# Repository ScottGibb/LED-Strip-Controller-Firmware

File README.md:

# LED Strip Controller Firmware

<!-- markdown-link-check-disable -->
   
<!-- markdown-link-check-enable -->

## Summary

This repository contains all the firmware to control the LED Strip Controller Hardware variations. The firmware is written in C++ using the Arduino framework, originally I wanted to use the STM32 HAL Drivers, however, the STM32 Microcontrollers were cloned and this resulted in the Arduino framework being used. The firmware is designed to be as flexible as possible, whilst maintaining an easy-to-use interface. The firmware is designed to be used with the LED Strip Controller Software Applications that are described below. The firmware is designed to be used with different microcontrollers.

## System Architecture

As for the system architecture it's designed to be interacted with via a byte stream sent over an interface. At present there is a UART interface over USB. However, there are plans to utilize an IP interface over WiFi. The byte stream is then parsed by the firmware and the appropriate action is taken. The firmware is designed to be as flexible as possible, whilst maintaining an easy-to-use interface. The firmware is designed to be used with the LED Strip Controller Software Applications. The architecture of the full system is shown below:

## Project Structure

This Project uses the PlatformIO Build system and as such adheres to their build structure and folder structure, the project is split into multiple folders outlined as follows:

```shell
├───docs
├───include
├───lib
│   ├───Board Configurations
│   ├───Buttons
│   ├───Communications
│   ├───Communicators
│   ├───Light Drivers
│   ├───Light Handlers
│   ├───Memory Management
│   ├───Misc Peripherals
│   ├───System Configuration
│   ├───System State Management
│   └───User Mode Handlers
├───src
└───test
```

- docs: holds all diagrams and pictures related to the project
- include: Holds the main header file responsible for the high-level aspects of the project
- lib: contains all private libraries for the project.
- src: contains the main application source code
- test: contains all of the unit tests for the project.

## Firmware Design

The firmware is designed to utilize modern C++ principles and be fully object orientated. This was done to allow me to utilize the full power of the C++ language and also allow me to learn new features regarding the language. The class diagram for the firmware is shown below:

The firmware is split into multiple layers which follow this layer convention:

The idea behind this is that the Arduino layer is abstracted away from the rest of the firmware. This allows the firmware logic to be used across multiple platforms and prevents it from being tied into the Arduino framework.

## Memory Map

The system does require some onboard memory to utilize the User Mode system. This allows the user to create custom colour waveforms and thus create custom effects. The memory map for the STM32F103C8T6 microcontroller is shown below:

## Building the Project

This project uses the PlatformIO Build system and as such can be built using the PlatformIO IDE or the PlatformIO CLI. For this simply clone this repository and open the folder using the PlatformIO plugin in VSCode. The IDE should then flag and install all the dependencies based on the platform.ini file.

- [PlatformIO](https://platformio.org/)
- [Visual Studio Code](https://code.visualstudio.com/)
- [PlatformIO Plugin for VSCode](https://marketplace.visualstudio.com/items?itemName=platformio.platformio-ide)

## Linting the project

You will need NodeJS and Docker installed. Once these are installed you can run the following command to lint the project:

```bash
npx mega-linter-runner
```

## LED Strip Controller Repository Links

- [Manifest](https://github.com/ScottGibb/LED-Strip-Controller-Manifest) This repository contains the manifest file for the LED Strip Controller project. Which allows the cloning of all the repositories in one go.
- [Hardware](https://github.com/ScottGibb/LED-Strip-Controller-Hardware) This repository contains the hardware design files for the LED Strip Controller project.
- [Firmware](https://github.com/ScottGibb/LED-Strip-Controller-Firmware) This repository contains the firmware for the LED Strip Controller project.
- [Software](https://github.com/ScottGibb/LED-Strip-Controller-Software) This repository contains the software for the LED Strip Controller project.

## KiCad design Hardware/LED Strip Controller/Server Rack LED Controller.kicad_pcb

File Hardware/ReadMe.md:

# LED Strip Controller Hardware
# Summary
The hardware was developed using veroboard first to prove the concept and then a PCB was designed with extra features that include: reduced form factor, over current/voltage protection circuitry, better thermal and EMI management.
# Design
The design consists of two PCBs, one which is the LED controller and an optional Buttons Controller daughter board. The 3D Printed case utilises both however, if the user decided that they only wanted to use the device through USB then the board could be removed.

## LED Strip Controller

The LED Strip Controller hardware is responsible for controlling the LEDs along with maintaining the system. This hardware should be capable of driving a variety of different light strips and protecting the whole board from short circuits and over voltages. The 3D render of the PCB is shown below:

## Buttons Controller
As for the Buttons Controller board, this is a simple PCB board with buttons, that can be added to the main board through a simple ribbon cable. This is done so that optional buttons can be added to the system. The 3D render of the PCB is shown below:

## 3D Printed Case Assembly

As for containing the hardware, a 3D printable case was designed and is shown below:

## Cable Wiring

# Improvements

# Useful Links
- [XT60 Connectors](https://www.aliexpress.com/item/1005004111518826.html?spm=a2g0o.order_list.0.0.44851802WtcK2c)
- [Terminal Crimps](https://www.aliexpress.com/item/1005004040825209.html?spm=a2g0o.productlist.0.0.7b09618cNrzGIX&algo_pvid=1400a7b4-9197-4d6a-b152-92a1a64300d6&algo_exp_id=1400a7b4-9197-4d6a-b152-92a1a64300d6-1&pdp_ext_f=%7B%22sku_id%22%3A%2212000028334234012%22%7D&pdp_npi=2%40dis%21GBP%216.94%215.2%21%21%21%21%21%402100bddb16647521768224542ea791%2112000028334234012%21sea&curPageLogUid=0NObb2zgCZaC)
- [Ferrel Crimps](https://www.aliexpress.com/item/1005004283026574.html?spm=a2g0o.detail.1000060.1.2b025a79uxZBof&gps-id=pcDetailBottomMoreThisSeller&scm=1007.13339.291025.0&scm_id=1007.13339.291025.0&scm-url=1007.13339.291025.0&pvid=82c1f2f2-f4eb-4113-b474-5a5eedb67d54&_t=gps-id:pcDetailBottomMoreThisSeller,scm-url:1007.13339.291025.0,pvid:82c1f2f2-f4eb-4113-b474-5a5eedb67d54,tpp_buckets:668%232846%238114%231999&pdp_ext_f=%7B%22sku_id%22%3A%2212000028621229126%22%2C%22sceneId%22%3A%223339%22%7D&pdp_npi=2%40dis%21GBP%218.57%215.57%21%21%21%21%21%40211b444016647521812691593e8c0a%2112000028621229126%21rec)
- [Switches](https://www.aliexpress.com/item/32743866390.html?spm=a2g0o.productlist.0.0.3cd4700cNdYXJ6&algo_pvid=e6b88297-a8ce-45f8-93eb-8b976bdea822&algo_exp_id=e6b88297-a8ce-45f8-93eb-8b976bdea822-3&pdp_ext_f=%7B%22sku_id%22%3A%2212000029574447281%22%7D&pdp_npi=2%40dis%21GBP%210.39%210.25%21%21%210.82%21%21%400b0a0ae216647521586066114e5989%2112000029574447281%21sea&curPageLogUid=3X8Abgou2M2X)

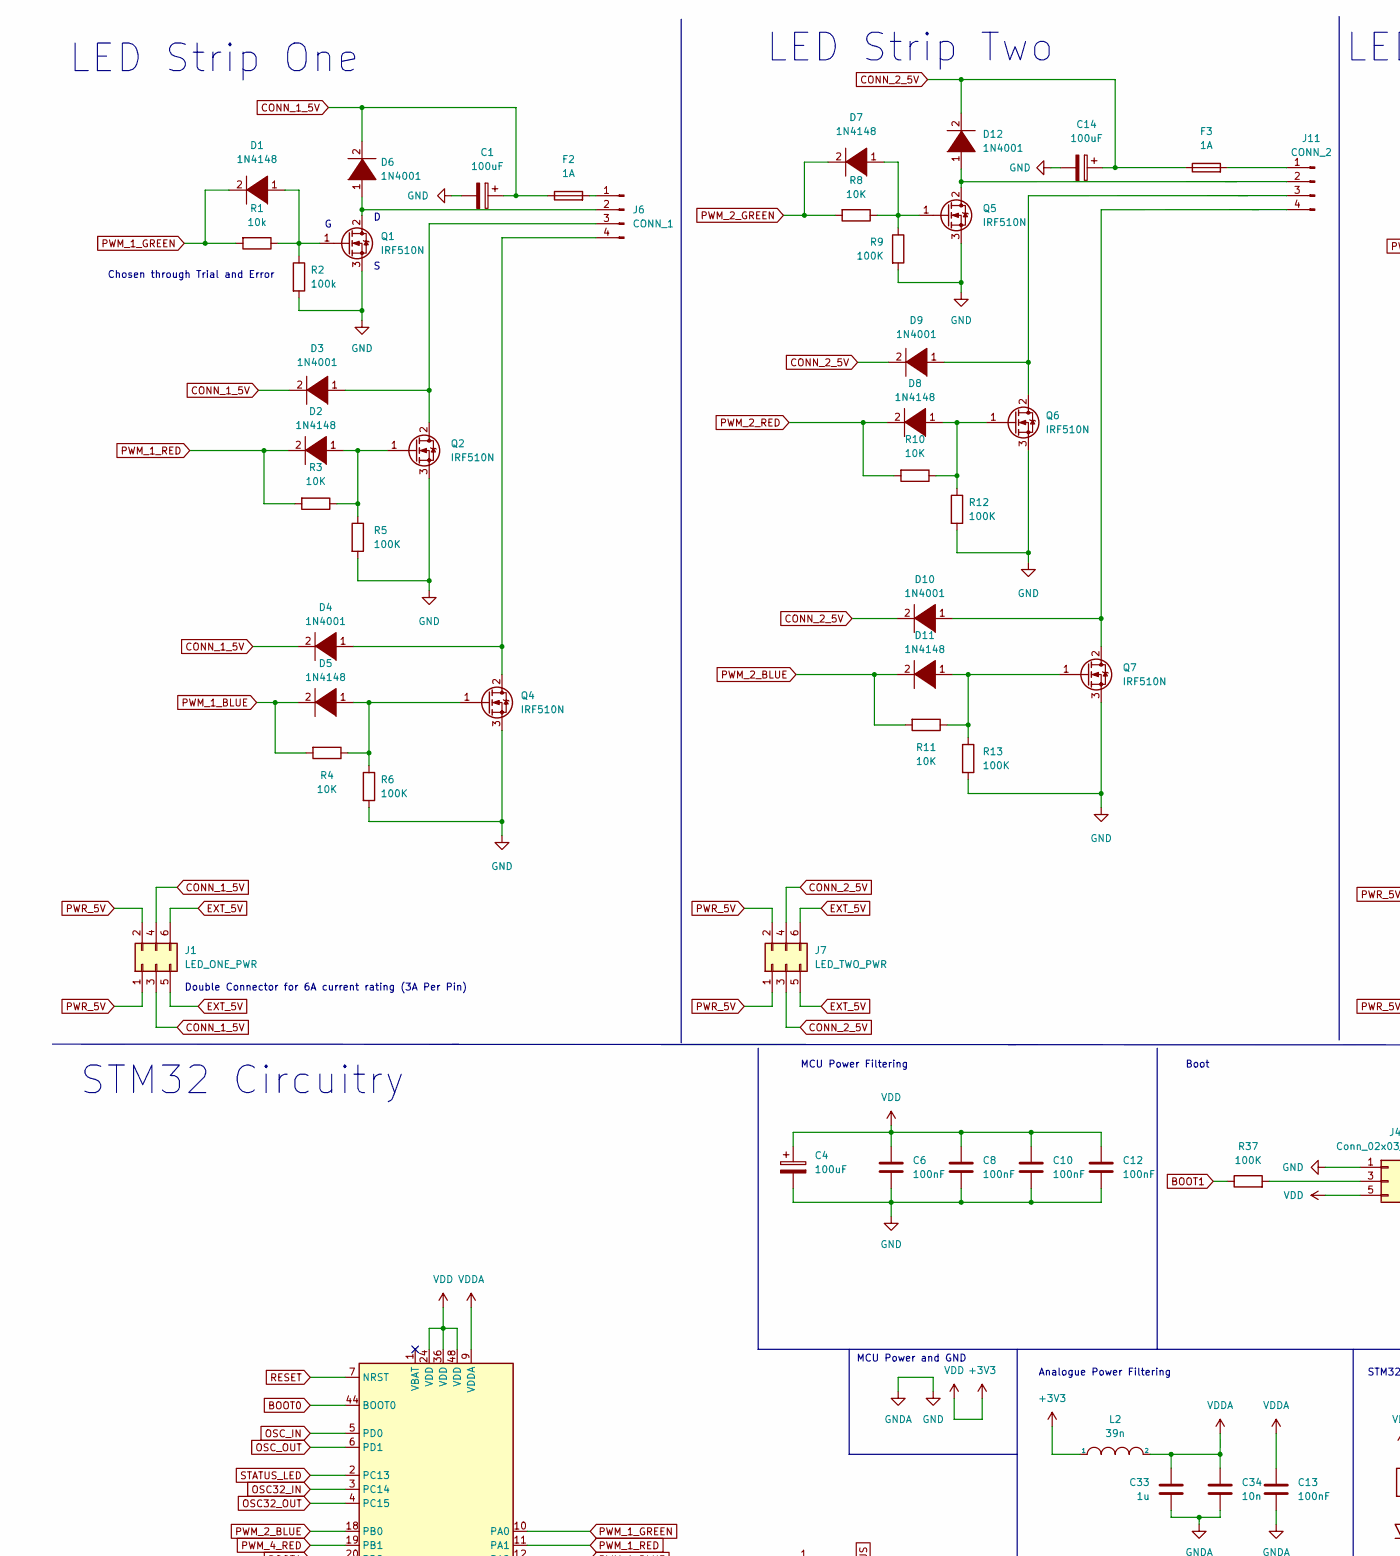
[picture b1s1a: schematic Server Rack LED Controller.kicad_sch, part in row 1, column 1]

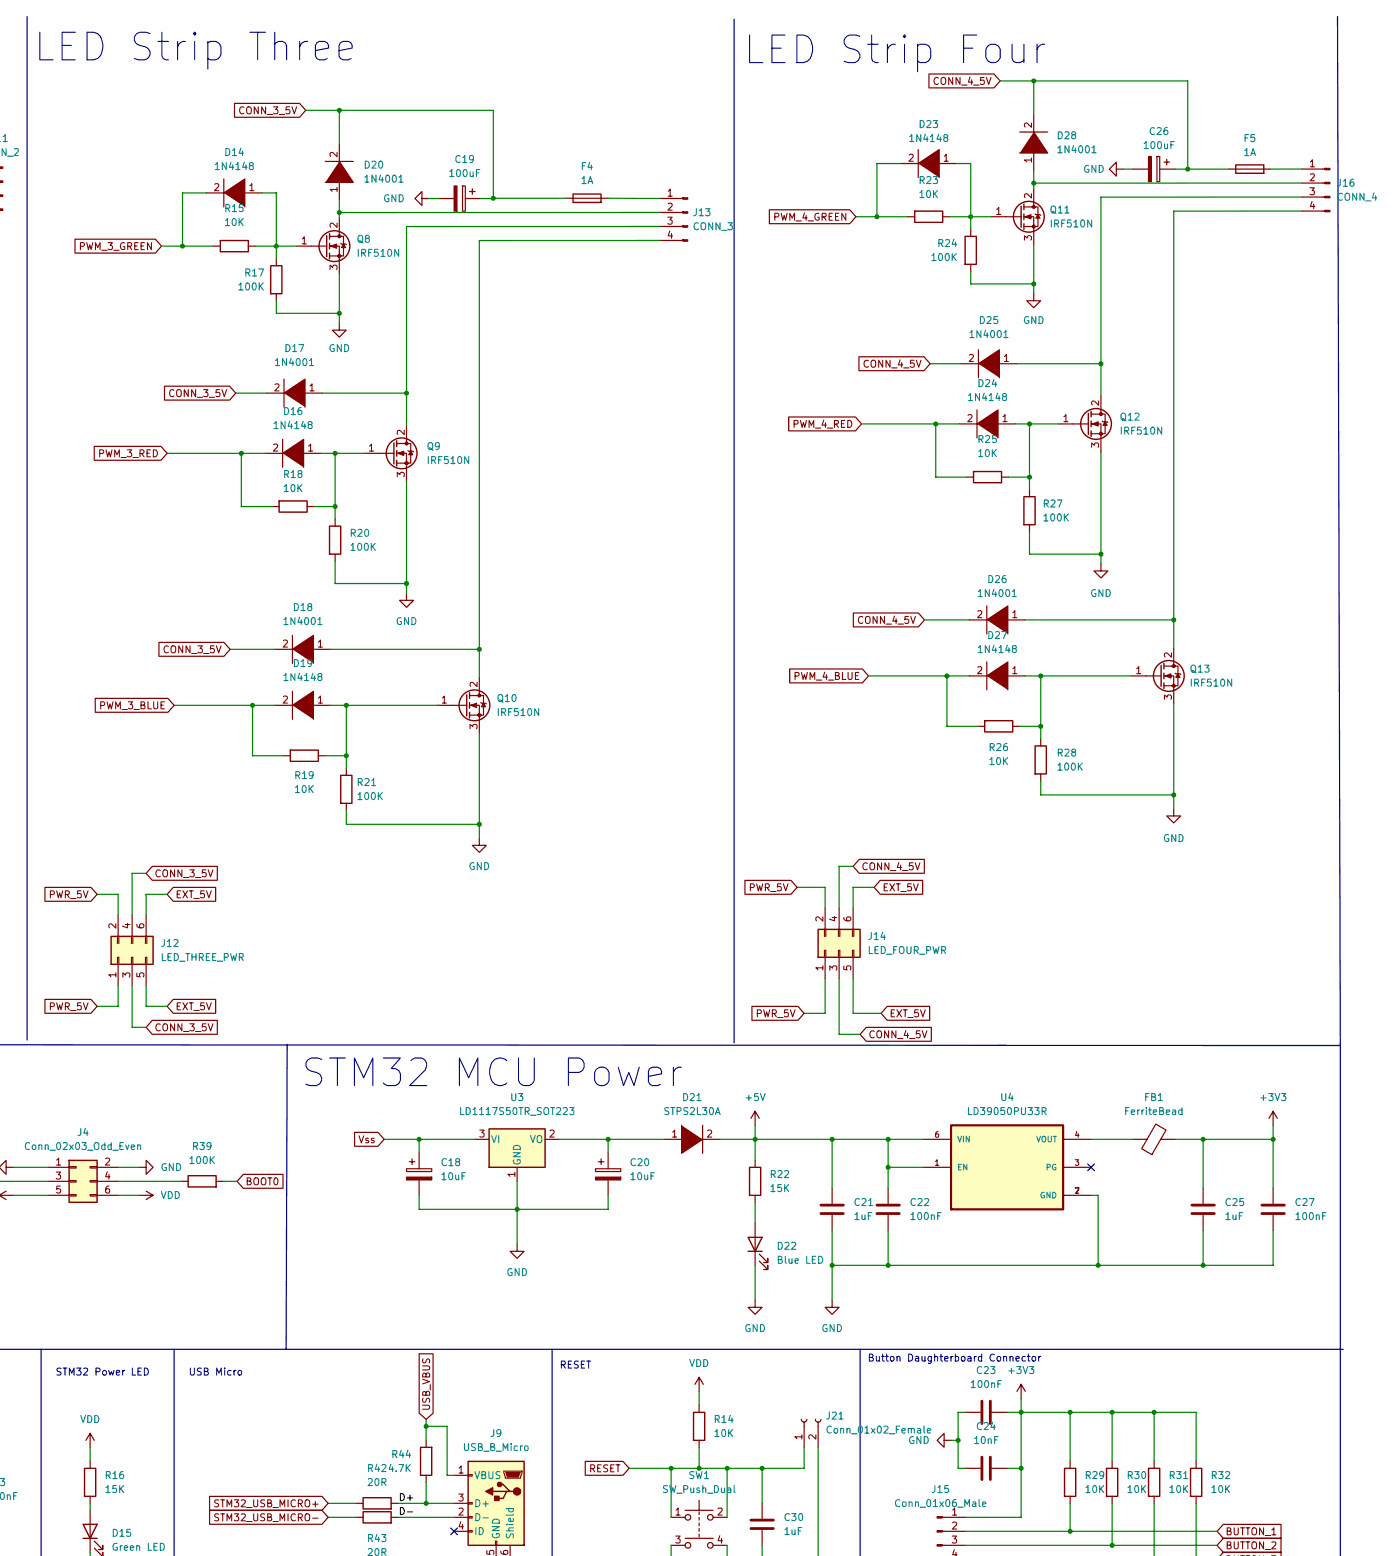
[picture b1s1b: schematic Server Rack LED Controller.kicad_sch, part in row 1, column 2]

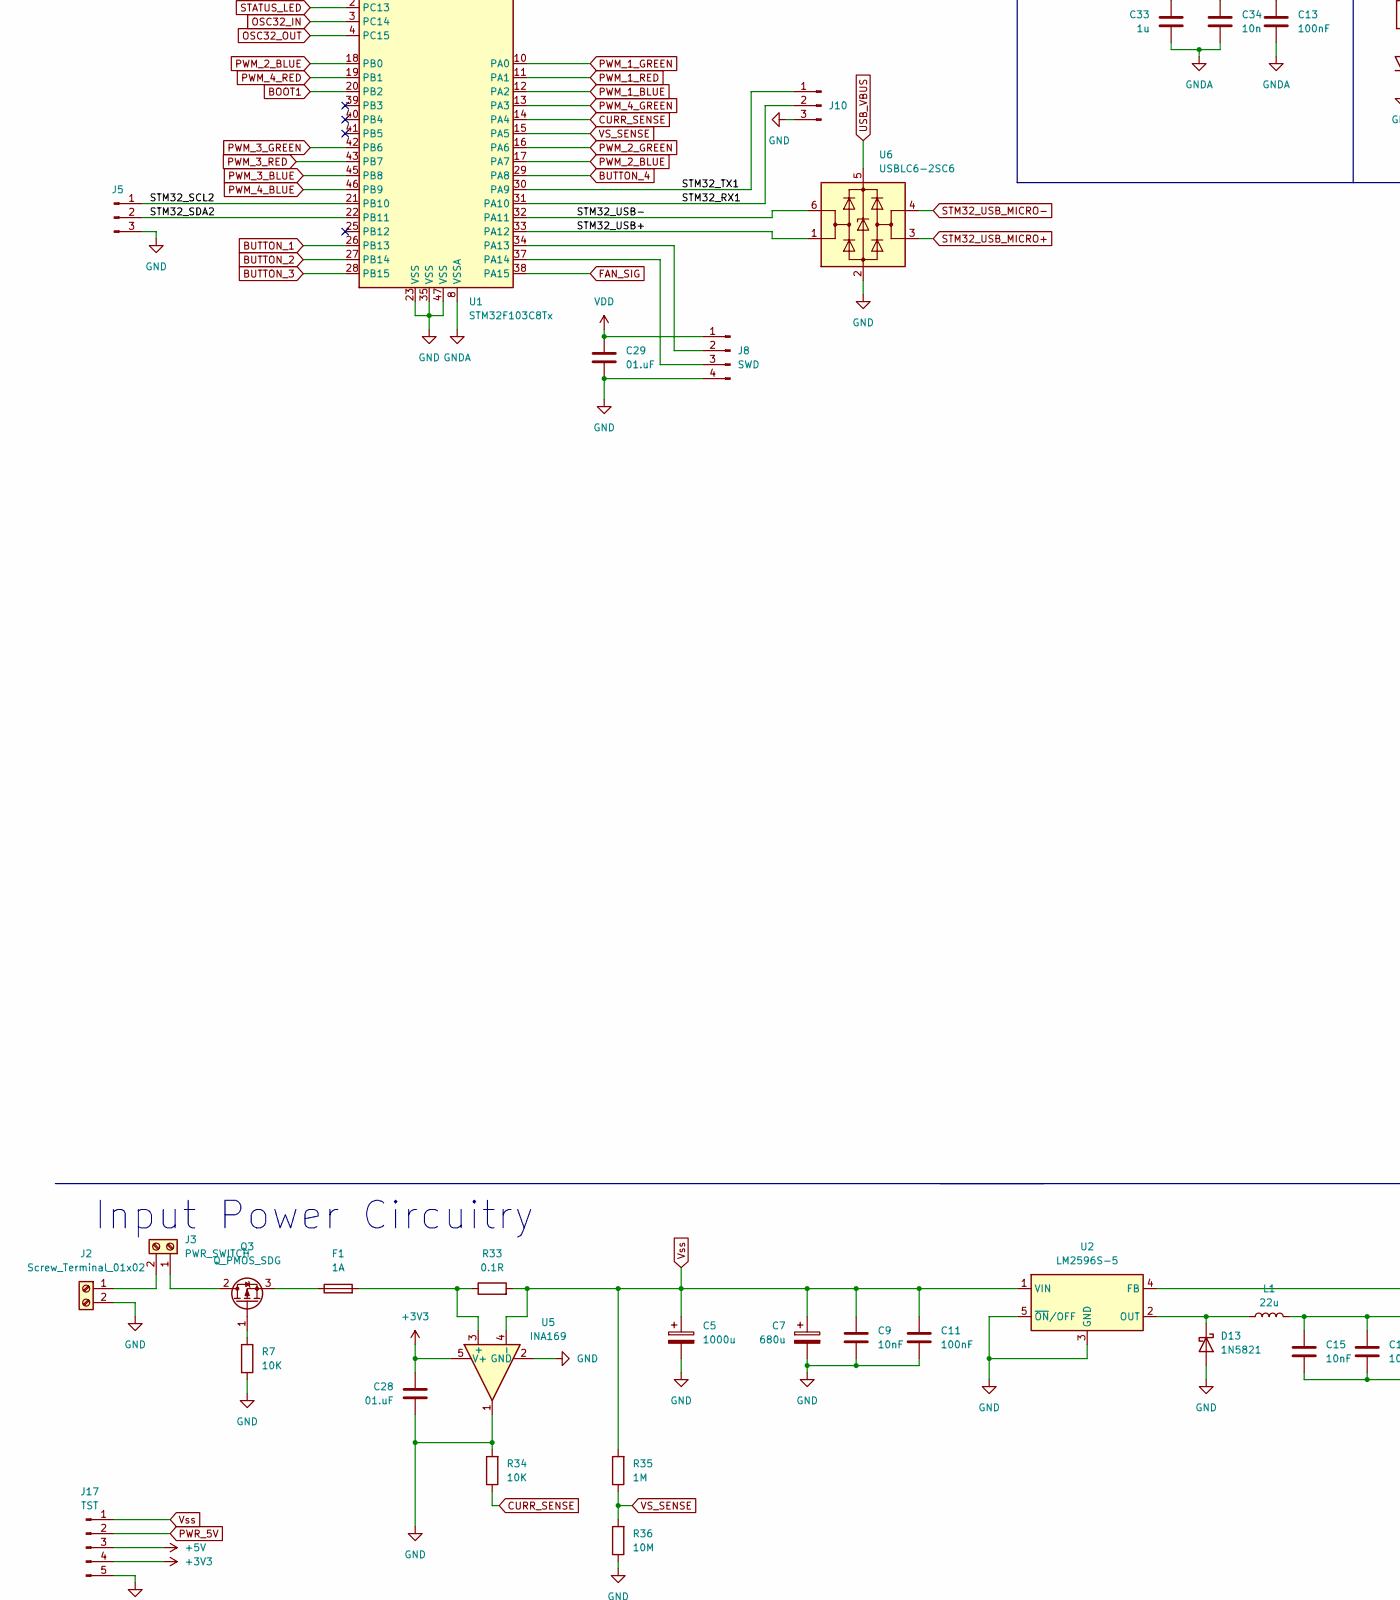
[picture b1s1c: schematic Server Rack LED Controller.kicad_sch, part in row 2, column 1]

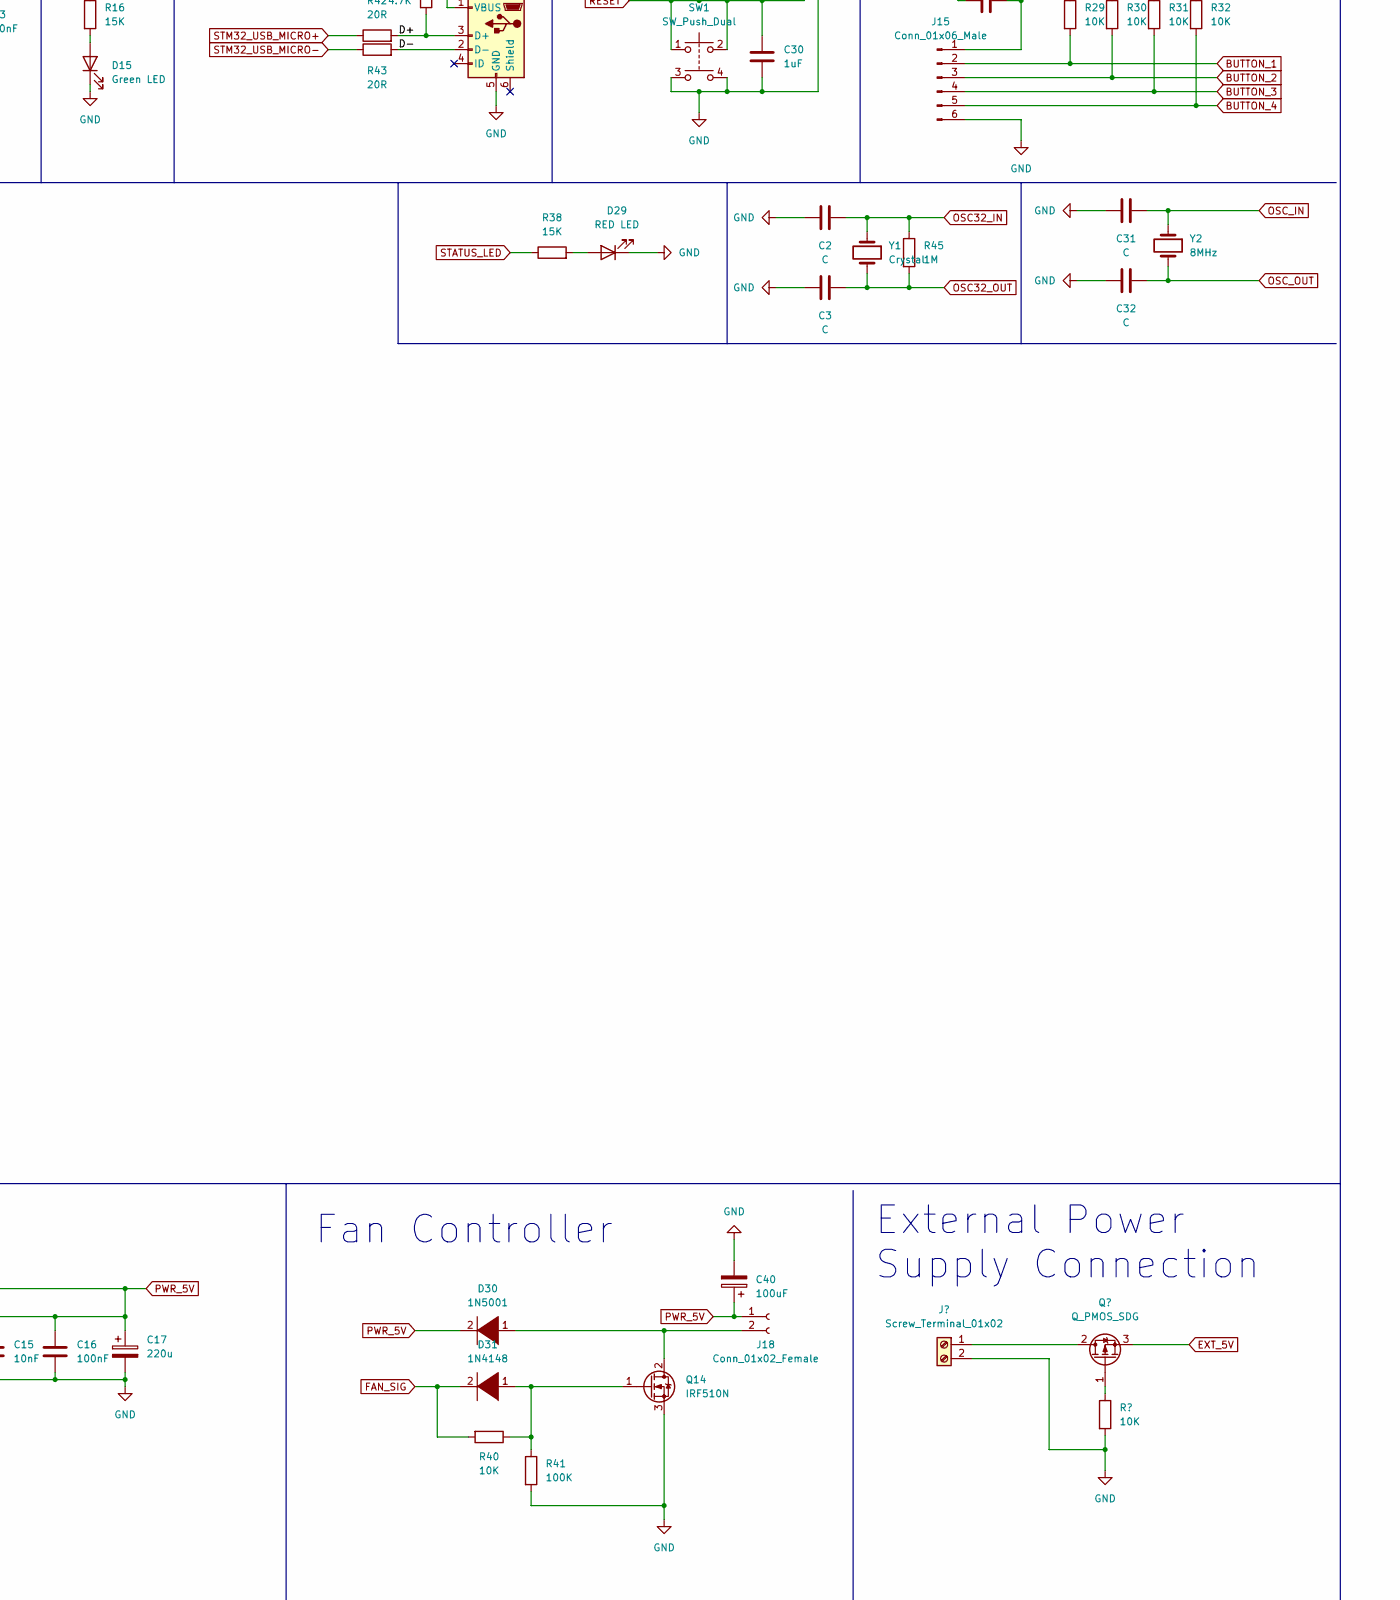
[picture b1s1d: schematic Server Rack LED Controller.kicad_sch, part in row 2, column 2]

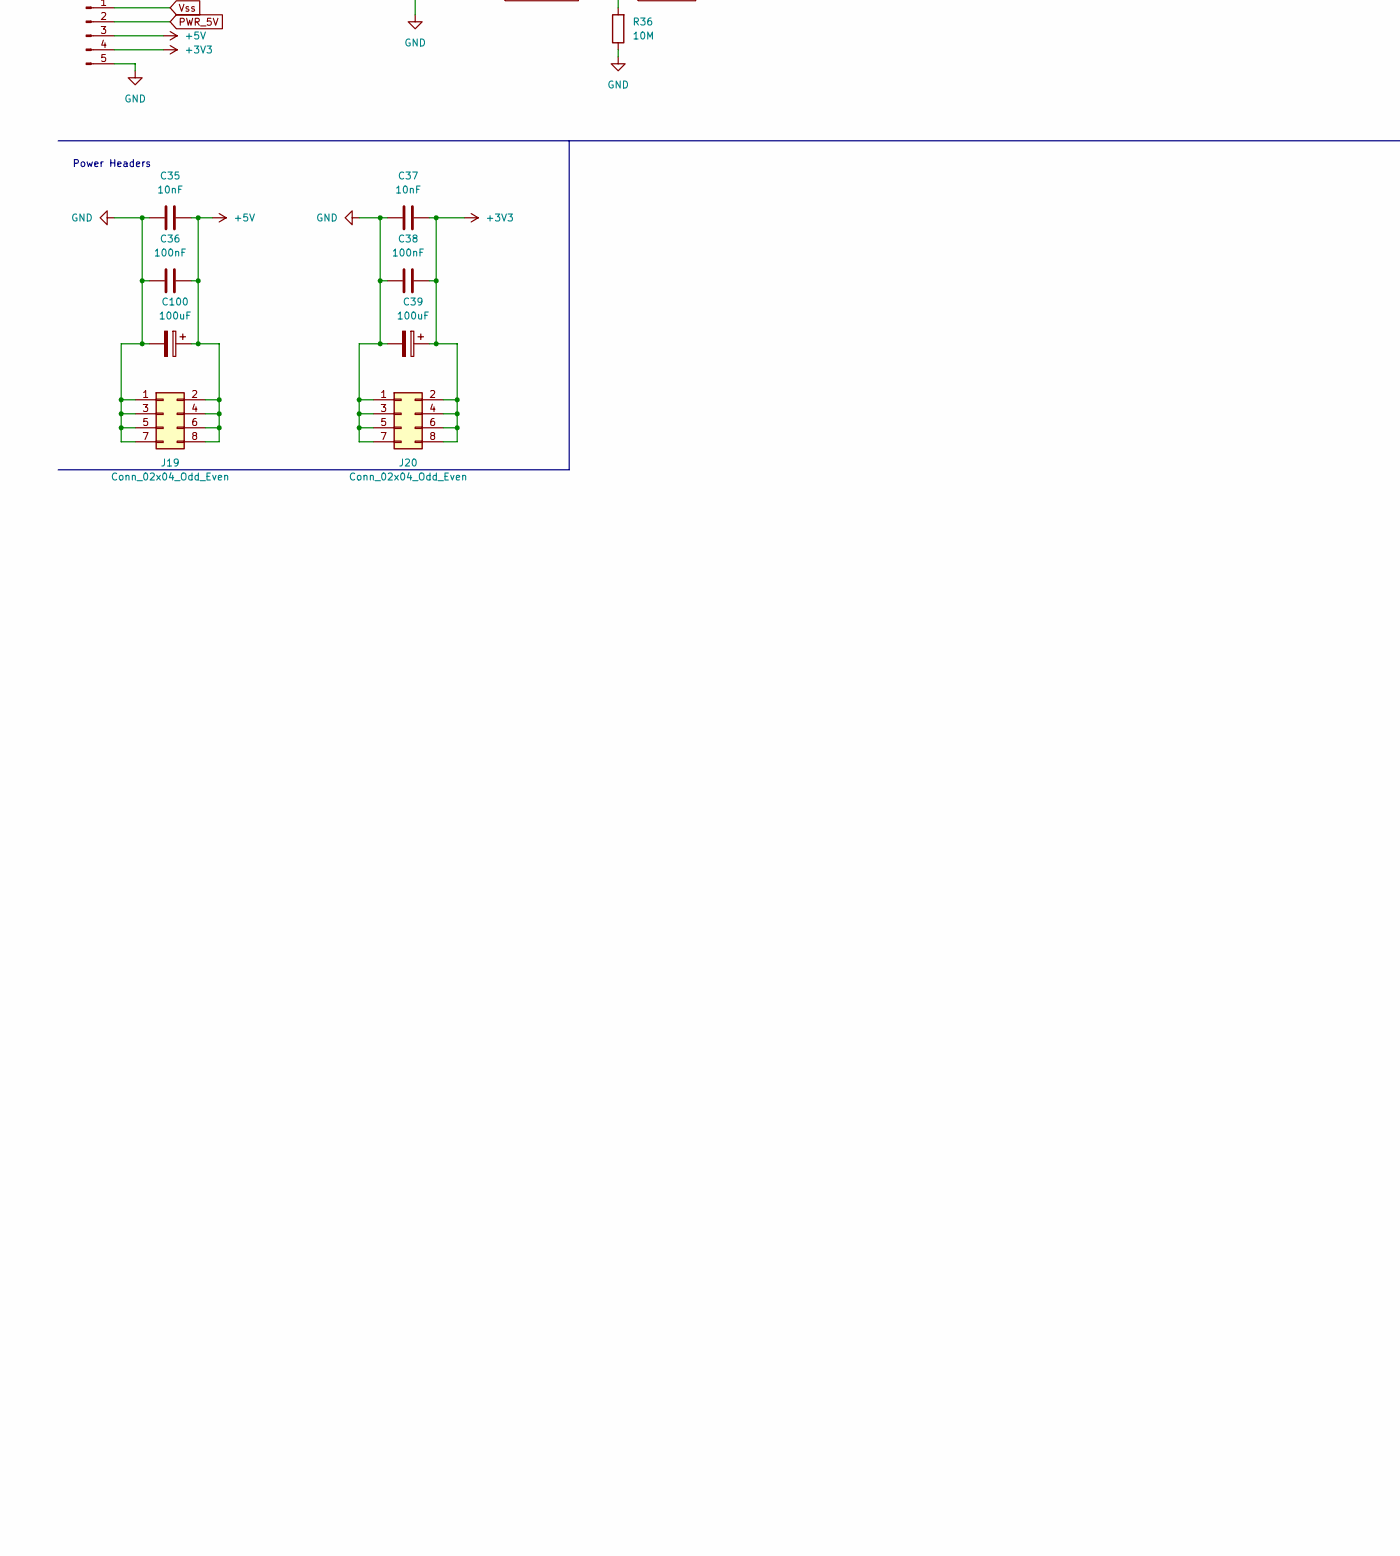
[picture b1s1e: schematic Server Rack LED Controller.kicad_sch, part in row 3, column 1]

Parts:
C1, C26, C40: 100uF; CP_Elec_10x10.5
C2, C3, C31, C32: C; C_1206_3216Metric
C4, C14, C19: 100uF; CP_Elec_10x10
C5: 1000u; CP_Elec_10x10.5; LCSC C263979
C6, C8, C10, C12, C13, C22, C23, C27: 100nF; C_1206_3216Metric
C7: 680u; CP_Elec_6.3x7.7; LCSC C249987
C9, C15, C35, C37: 10nF; C_1206_3216Metric_Pad1.33x1.80mm_HandSolder; LCSC C1846
C11, C16, C36, C38: 100nF; C_1206_3216Metric_Pad1.33x1.80mm_HandSolder; LCSC C93194
C17: 220u; CP_Elec_6.3x7.7; LCSC C127968
C18: 10uF; CP_Elec_10x10.5
C20: 10uF; CP_Elec_10x10
C21, C25, C30: 1uF; C_1206_3216Metric
C24: 10nF; C_1206_3216Metric
C28, C29: 01.uF; C_1206_3216Metric
C33: 1u; C_1206_3216Metric
C34: 10n; C_1206_3216Metric
C39, C100: 100uF; CP_Elec_6.3x7.7; LCSC C127968
D1: 1N4148; D_SOD-323; LCSC C2128
D2, D5, D7, D8, D11, D14, D16, D19, D23, D24, D27, D31: 1N4148; D_SOD-323
D3, D4: 1N4001; D_SOD-123F
D6: 1N4001; D_SOD-123F; LCSC C162732
D9, D10, D12, D17, D18, D20, D25, D26, D28: 1N4001; D_SMA
D13: 1N5821; D_SMA; LCSC C8678
D15: Green LED; LED_1206_3216Metric
D21: STPS2L30A
D22: Blue LED; LED_1206_3216Metric
D29: RED LED; LED_1206_3216Metric
D30: 1N5001; D_SMA
F1, F2, F3, F4, F5: 1A; Fuseholder_Clip-5x20mm_Littelfuse_111_Inline_P20.00x5.00mm_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
FB1: FerriteBead
J1: LED_ONE_PWR; PinHeader_2x03_P2.54mm_Vertical
J2: Screw_Terminal_01x02; TerminalBlock_Phoenix_MKDS-1,5-2-5.08_1x02_P5.08mm_Horizont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
J3: PWR_SWITCH; TerminalBlock_Phoenix_MKDS-1,5-2-5.08_1x02_P5.08mm_Horizont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
J4: Conn_02x03_Odd_Even; PinHeader_2x03_P2.54mm_Vertical
J5: Conn_01x03_Female; PinHeader_1x03_P2.54mm_Vertical
J6: CONN_1; JST_EH_B4B-EH-A_1x04_P2.50mm_Vertical
J7: LED_TWO_PWR; PinHeader_2x03_P2.54mm_Vertical
J8: SWD; PinHeader_1x04_P2.54mm_Vertical
J9: USB_B_Micro; USB_Micro-B_Molex-105017-0001
J10: UART; PinHeader_1x03_P2.54mm_Vertical
J11: CONN_2; JST_EH_B4B-EH-A_1x04_P2.50mm_Vertical
J12: LED_THREE_PWR; PinHeader_2x03_P2.54mm_Vertical
J13: CONN_3; JST_EH_B4B-EH-A_1x04_P2.50mm_Vertical
J14: LED_FOUR_PWR; PinHeader_2x03_P2.54mm_Vertical
J15: Conn_01x06_Male; JST_EH_B6B-EH-A_1x06_P2.50mm_Vertical
J16: CONN_4; JST_EH_B4B-EH-A_1x04_P2.50mm_Vertical
J17: TST; PinHeader_1x05_P2.54mm_Vertical
J18, J21: Conn_01x02_Female; JST_EH_B2B-EH-A_1x02_P2.50mm_Vertical
J19, J20: Conn_02x04_Odd_Even; PinHeader_2x04_P2.54mm_Vertical
L1: 22u; L_12x12mm_H8mm; LCSC C339950
L2: 39n
Q1: IRF510N; TO-263-3_TabPin2
Q2, Q4, Q5, Q6, Q7, Q8, Q9, Q10, Q11, Q12, Q13, Q14: IRF510N; TO-263-2
Q3: Q_PMOS_SDG; TO-252-3_TabPin2; LCSC C33903
R1: 10k; R_1206_3216Metric
R2: 100k; R_1206_3216Metric
R3, R4, R8, R10, R11, R14, R15, R18, R19, R23, R25, R26, R29, R30, R31, R32, R34, R40: 10K; R_1206_3216Metric
R5, R6, R9, R12, R13, R17, R20, R21, R24, R27, R28, R37, R39, R41: 100K; R_1206_3216Metric
R7: 10K; R_1206_3216Metric_Pad1.30x1.75mm_HandSolder; LCSC C17902
R16, R22, R38: 15K; R_1206_3216Metric
R33: 0.1R; R_2512_6332Metric
R35, R45: 1M; R_1206_3216Metric
R36: 10M; R_1206_3216Metric
R42, R43: 20R; R_1206_3216Metric
R44: 4.7K; R_1206_3216Metric
SW1: SW_Push_Dual; SW_PUSH_6mm
U1: STM32F103C8Tx; LQFP-48_7x7mm_P0.5mm
U2: LM2596S-5; TO-263-5_TabPin3; LCSC C347421
U3: LD1117S50TR_SOT223; SOT-223-3_TabPin2
U4: LD39050PU33R; DFN-6-1EP_3x3mm_P0.95mm_EP1.7x2.6mm; DIGI-KEY_PART_NUMBER 497-8716-1-ND
U5: INA169; SOT-23-5
U6: USBLC6-2SC6; SOT-23-6
Y1: Crystal
Y2: 8MHz

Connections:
+3V3: C4.1, C6.1, C8.1, C10.1, C12.1, C23.1, C24.1, C25.1, C27.1, C28.1, C29.1, C37.2, C38.1, C39.1, FB1.2, J4.5, J4.6, J8.1, J15.1, J17.4, J20.2, J20.4, J20.6, J20.8, L2.1, R14.1, R16.1, R29.1, R30.1, R31.1, R32.1, U1.24 (VDD), U1.36 (VDD), U1.48 (VDD), U5.5 (V+)
+5V: C21.1, C22.1, C35.2, C36.1, C100.1, D21.2 (A), J17.3, J19.2, J19.4, J19.6, J19.8, R22.1, U4.1 (EN), U4.6 (VIN)
/D+: J9.3 (D+), R42.2, R44.1
/D-: J9.2 (D-), R43.2
/STM32_RX1: J10.2, U1.31 (PA10); also elsewhere on the board
/STM32_SCL2: J5.1, U1.21 (PB10)
/STM32_SDA2: J5.2, U1.22 (PB11)
/STM32_TX1: J10.1, U1.30 (PA9); also elsewhere on the board
/STM32_USB+: U1.33 (PA12), U6.1 (I/O1)
/STM32_USB-: U1.32 (PA11), U6.6 (I/O1)
BOOT0: R39.2, U1.44 (BOOT0)
BOOT1: R37.1, U1.20 (PB2)
BUTTON_1: J15.2, R29.2, U1.26 (PB13)
BUTTON_2: J15.3, R30.2, U1.27 (PB14)
BUTTON_3: J15.4, R31.2, U1.28 (PB15)
BUTTON_4: J15.5, R32.2, U1.29 (PA8)
CONN_1_5V: C1.1, D3.2 (A), D4.2 (A), D6.2 (A), F2.1, J1.3, J1.4
CONN_2_5V: C14.1, D9.2 (A), D10.2 (A), D12.2 (A), F3.1, J7.3, J7.4
CONN_3_5V: C19.1, D17.2 (A), D18.2 (A), D20.2 (A), F4.1, J12.3, J12.4
CONN_4_5V: C26.1, D25.2 (A), D26.2 (A), D28.2 (A), F5.1, J14.3, J14.4
CURR_SENSE: R34.1, U1.14 (PA4)
EXT_5V: J1.5, J1.6, J7.5, J7.6, J12.5, J12.6, J14.5, J14.6; also elsewhere on the board
FAN_SIG: D31.2 (A), R40.2, U1.38 (PA15)
GND: C1.2, C2.2, C3.2, C4.2, C5.2, C6.2, C7.2, C8.2, C9.2, C10.2, C11.2, C12.2, C13.2, C14.2, C15.2, C16.2, C17.2, C18.2, C19.2, C20.2, C21.2, C22.2, C23.2, C24.2, C25.2, C26.2, C27.2, C28.2, C29.2, C30.2, C31.2, C32.2, C33.2, C34.2, C35.1, C36.2, C37.1, C38.2, C39.2, C40.2, C100.2, D13.2 (A), D15.1 (K), D22.1 (K), D29.1 (K), J2.2, J4.1, J4.2, J5.3, J8.4, J9.5 (GND), J10.3, J15.6, J17.5, J19.1, J19.3, J19.5, J19.7, J20.1, J20.3, J20.5, J20.7, J21.2, Q1.3 (S), Q2.3 (S), Q4.3 (S), Q5.3 (S), Q6.3 (S), Q7.3 (S), Q8.3 (S), Q9.3 (S), Q10.3 (S), Q11.3 (S), Q12.3 (S), Q13.3 (S), Q14.3 (S), R2.2, R5.2, R6.2, R7.2, R9.2, R12.2, R13.2, R17.2, R20.2, R21.2, R24.2, R27.2, R28.2, R34.2, R36.1, R41.2, SW1.3, SW1.4, U1.8 (VSSA), U1.23 (VSS), U1.35 (VSS), U1.47 (VSS), U2.3 (GND), U2.5 (~ON/OFF), U3.1 (GND), U4.2 (GND), U4.7 (GND), U5.1, U5.2 (GND), U6.2 (GND); also elsewhere on the board
unnamed: C20.1, D21.1 (K), U3.2 (VO)
unnamed: D1.1 (K), Q1.1 (G), R1.1, R2.1
unnamed: D2.1 (K), Q2.1 (G), R3.1, R5.1
unnamed: D3.1 (K), J6.3, Q2.2 (D)
unnamed: D4.1 (K), J6.4, Q4.2 (D)
unnamed: D5.1 (K), Q4.1 (G), R4.1, R6.1
unnamed: D6.1 (K), J6.2, Q1.2 (D)
unnamed: D7.1 (K), Q5.1 (G), R8.1, R9.1
unnamed: D8.1 (K), Q6.1 (G), R10.1, R12.1
unnamed: D9.1 (K), J11.3, Q6.2 (D)
unnamed: D10.1 (K), J11.4, Q7.2 (D)
unnamed: D11.1 (K), Q7.1 (G), R11.1, R13.1
unnamed: D12.1 (K), J11.2, Q5.2 (D)
unnamed: D13.1 (K), L1.1, U2.2 (OUT)
unnamed: D14.1 (K), Q8.1 (G), R15.1, R17.1
unnamed: D15.2 (A), R16.2
unnamed: D16.1 (K), Q9.1 (G), R18.1, R20.1
unnamed: D17.1 (K), J13.3, Q9.2 (D)
unnamed: D18.1 (K), J13.4, Q10.2 (D)
unnamed: D19.1 (K), Q10.1 (G), R19.1, R21.1
unnamed: D20.1 (K), J13.2, Q8.2 (D)
unnamed: D22.2 (A), R22.2
unnamed: D23.1 (K), Q11.1 (G), R23.1, R24.1
unnamed: D24.1 (K), Q12.1 (G), R25.1, R27.1
unnamed: D25.1 (K), J16.3, Q12.2 (D)
unnamed: D26.1 (K), J16.4, Q13.2 (D)
unnamed: D27.1 (K), Q13.1 (G), R26.1, R28.1
unnamed: D28.1 (K), J16.2, Q11.2 (D)
unnamed: D29.2 (A), R38.2
unnamed: D30.1 (K), J18.2, Q14.2 (D)
unnamed: D31.1 (K), Q14.1 (G), R40.1, R41.1
unnamed: F1.1, Q3.3 (S)
unnamed: F1.2, R33.1, U5.3 (+)
unnamed: FB1.1, U4.4 (VOUT)
unnamed: J2.1, J3.2
unnamed: J3.1, Q3.2 (D)
unnamed: J4.3, R37.2
unnamed: J4.4, R39.1
unnamed: F2.2, J6.1
unnamed: J8.2, U1.34 (PA13)
unnamed: J8.3, U1.37 (PA14)
unnamed: F3.2, J11.1
unnamed: F4.2, J13.1
unnamed: F5.2, J16.1
unnamed: Q3.1 (G), R7.1
OSC32_IN: C2.1, R45.1, U1.3 (PC14), Y1.1
OSC32_OUT: C3.1, R45.2, U1.4 (PC15), Y1.2
OSC_IN: C31.1, U1.5 (PD0), Y2.1
OSC_OUT: C32.1, U1.6 (PD1), Y2.2
PWM_1_BLUE: D5.2 (A), R4.2, U1.12 (PA2)
PWM_1_GREEN: D1.2 (A), R1.2, U1.10 (PA0)
PWM_1_RED: D2.2 (A), R3.2, U1.11 (PA1)
PWM_2_BLUE: D11.2 (A), R11.2, U1.17 (PA7), U1.18 (PB0)
PWM_2_GREEN: D7.2 (A), R8.2, U1.16 (PA6)
PWM_2_RED: D8.2 (A), R10.2
PWM_3_BLUE: D19.2 (A), R19.2, U1.45 (PB8)
PWM_3_GREEN: D14.2 (A), R15.2, U1.42 (PB6)
PWM_3_RED: D16.2 (A), R18.2, U1.43 (PB7)
PWM_4_BLUE: D27.2 (A), R26.2, U1.46 (PB9)
PWM_4_GREEN: D23.2 (A), R23.2, U1.13 (PA3)
PWM_4_RED: D24.2 (A), R25.2, U1.19 (PB1)
PWR_5V: C15.1, C16.1, C17.1, C40.1, D30.2 (A), J1.1, J1.2, J7.1, J7.2, J12.1, J12.2, J14.1, J14.2, J17.2, J18.1, L1.2, U2.4 (FB)
RESET: C30.1, J21.1, R14.2, SW1.1, SW1.2, U1.7 (NRST)
STATUS_LED: R38.1, U1.2 (PC13)
STM32_USB_MICRO+: R42.1, U6.3 (I/O2)
STM32_USB_MICRO-: R43.1, U6.4 (I/O2)
USB_VBUS: J9.1 (VBUS), R44.2, U6.5 (VBUS)
VDDA: C13.1, C33.1, C34.1, L2.2, U1.9 (VDDA)
VS_SENSE: R35.1, R36.2, U1.15 (PA5)
Vss: C5.1, C7.1, C9.1, C11.1, C18.1, J17.1, R33.2, R35.2, U2.1 (VIN), U3.3 (VI), U5.4 (-)

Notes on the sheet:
MCU Power and GND
Power Headers
Double Connector for 6A current rating (3A Per Pin)
Chosen through Trial and Error
Button Daughterboard Connector
LED Strip Four
LED Strip Three
STM32 MCU Power
USB Micro
Analogue Power Filtering
LED Strip Two
Fan Controller
LED Strip One
Boot
Input Power Circuitry
External Power Supply Connection
RESET
MCU Power Filtering
STM32 Power LED
STM32 Circuitry

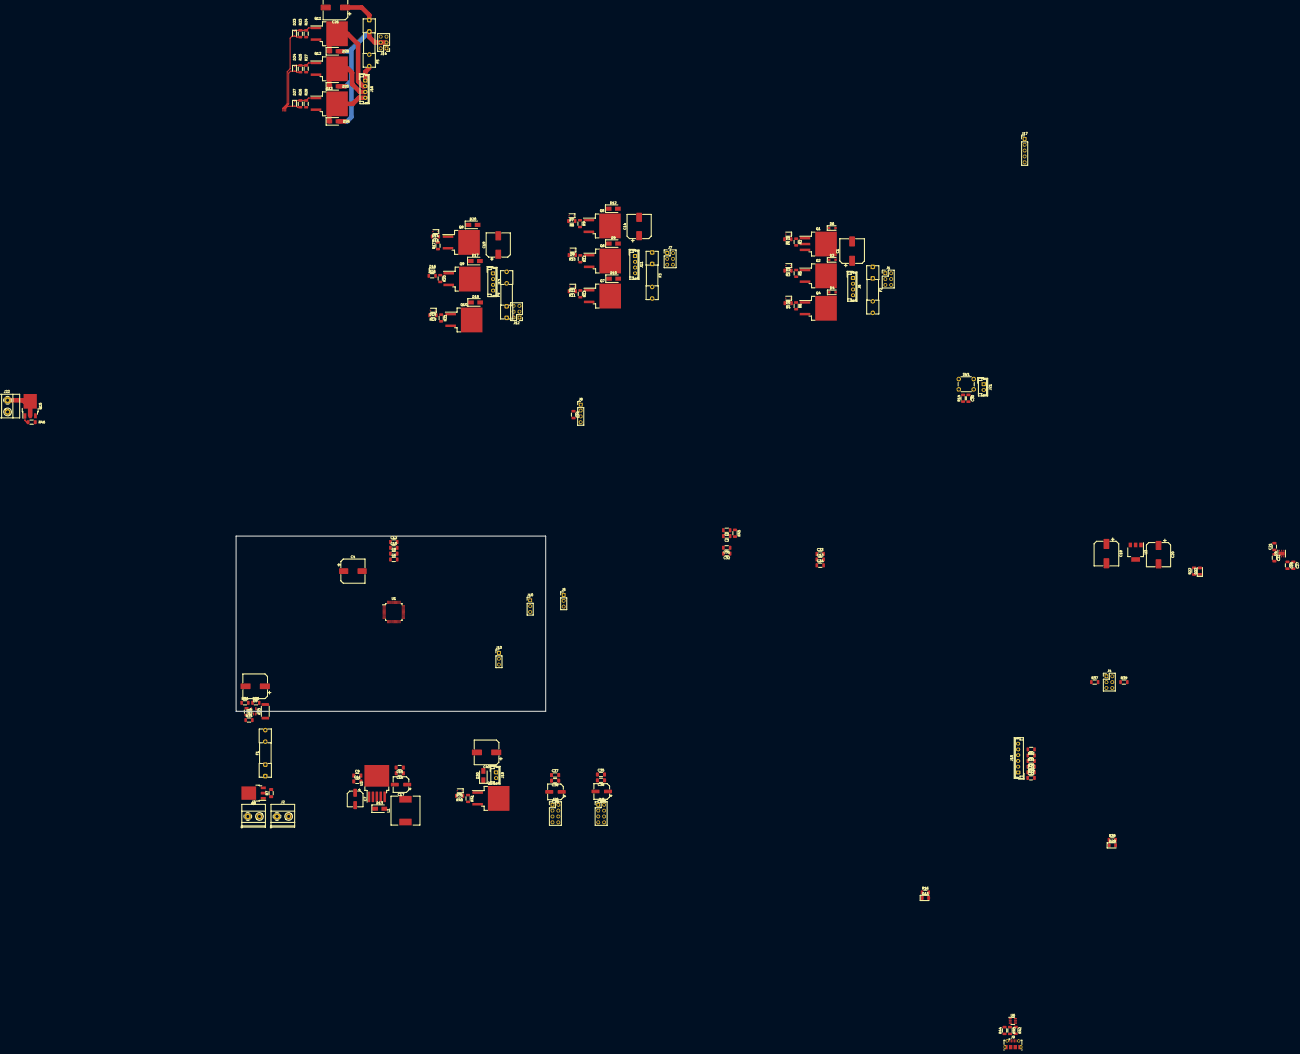
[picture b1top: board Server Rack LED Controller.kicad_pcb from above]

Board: 2 copper layers, 168 parts (0 on the bottom side), 95 nets.

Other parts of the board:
J10#2: UART; PinHeader_1x03_P2.54mm_Vertical
J22: Screw_Terminal_01x02; TerminalBlock_Phoenix_MKDS-1,5-2-5.08_1x02_P5.08mm_Horizont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
Q15: Q_PMOS_SDG; TO-252-3_TabPin2
R46: 10K; R_1206_3216Metric_Pad1.30x1.75mm_HandSolder

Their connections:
/STM32_RX1: J10#2.2; also elsewhere on the board
/STM32_TX1: J10#2.1; also elsewhere on the board
EXT_5V: Q15.3 (S); also elsewhere on the board
GND: J10#2.3, J22.2, R46.2; also elsewhere on the board
unnamed: J22.1, Q15.2 (D)
unnamed: Q15.1 (G), R46.1

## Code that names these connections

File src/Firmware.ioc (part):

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Mcu.Name=STM32F103C(8-B)Tx
Mcu.Package=LQFP48
Mcu.UserName=STM32F103C8Tx
PA0-WKUP.GPIOParameters=GPIO_Label
PA0-WKUP.GPIO_Label=PWM_1_GREEN
PA0-WKUP.Signal=S_TIM2_CH1_ETR
PA1.GPIOParameters=GPIO_Label
PA1.GPIO_Label=PWM_1_RED
PA1.Signal=S_TIM2_CH2
PA10.Mode=Asynchronous
PA10.Signal=USART1_RX
PA11.Mode=Device
PA11.Signal=USB_DM
PA12.Mode=Device
PA12.Signal=USB_DP
PA13.Mode=Serial_Wire
PA13.Signal=SYS_JTMS-SWDIO
PA14.Mode=Serial_Wire
PA14.Signal=SYS_JTCK-SWCLK
PA15.GPIOParameters=GPIO_Label
PA15.GPIO_Label=FAN_SIG
PA15.Signal=GPIO_Output
PA2.GPIOParameters=GPIO_Label
PA2.GPIO_Label=PWM_1_BLUE
PA2.Signal=S_TIM2_CH3
PA3.GPIOParameters=GPIO_Label
PA3.GPIO_Label=PWM_4_GREEN
PA3.Signal=S_TIM2_CH4
PA4.GPIOParameters=GPIO_Label
PA4.GPIO_Label=CURR_SENSE
PA4.Signal=ADCx_IN4
PA5.GPIOParameters=GPIO_Label
PA5.GPIO_Label=VS_SENSE
PA5.Signal=ADCx_IN5
PA6.GPIOParameters=GPIO_Label
PA6.GPIO_Label=PWM_2_GREEN
PA6.Signal=S_TIM3_CH1
PA7.GPIOParameters=GPIO_Label
PA7.GPIO_Label=PWM_2_RED
PA7.Signal=S_TIM3_CH2
PA8.Signal=GPIO_Input
PA9.Mode=Asynchronous
PA9.Signal=USART1_TX
PB0.GPIOParameters=GPIO_Label
PB0.GPIO_Label=PWM_2_BLUE
PB0.Signal=S_TIM3_CH3
PB1.GPIOParameters=GPIO_Label
PB1.GPIO_Label=PWM_4_RED
PB1.Signal=S_TIM3_CH4
PB10.Mode=I2C
PB10.Signal=I2C2_SCL
PB11.Mode=I2C
PB11.Signal=I2C2_SDA
PB13.Signal=GPIO_Input
PB14.Signal=GPIO_Input
PB15.Signal=GPIO_Input
PB2.GPIOParameters=GPIO_Label
PB2.GPIO_Label=BOOT
PB2.Signal=GPIO_Input
PB6.GPIOParameters=GPIO_Label
PB6.GPIO_Label=PWM_3_GREEN
PB6.Signal=S_TIM4_CH1
PB7.GPIOParameters=GPIO_Label
PB7.GPIO_Label=PWM_3_RED
PB7.Signal=S_TIM4_CH2
PB8.GPIOParameters=GPIO_Label
PB8.GPIO_Label=PWM_3_BLUE
PB8.Signal=S_TIM4_CH3
PB9.Signal=S_TIM4_CH4
PC13-TAMPER-RTC.Signal=GPIO_Output
PC14-OSC32_IN.Mode=LSE-External-Oscillator
PC14-OSC32_IN.Signal=RCC_OSC32_IN
PC15-OSC32_OUT.Mode=LSE-External-Oscillator
PC15-OSC32_OUT.Signal=RCC_OSC32_OUT
PD0-OSC_IN.Mode=HSE-External-Oscillator
PD0-OSC_IN.Signal=RCC_OSC_IN
PD1-OSC_OUT.Mode=HSE-External-Oscillator
PD1-OSC_OUT.Signal=RCC_OSC_OUT
RCC.SYSCLKFreq_VALUE=48000000
RCC.SYSCLKSource=RCC_SYSCLKSOURCE_PLLCLK
board=custom

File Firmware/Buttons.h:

/**
 * @file Buttons.h
 * @author Scott Gibb (smgibb@yahoo.com)
 * @brief Button Pins Defintions Header File
 * @version 0.1
 * @date 2022-10-03
 * 
 * @copyright Copyright (c) 2022
 * 
 */
#ifndef __BUTTONS__H_
#define __BUTTONS__H_

//Library Includes
#include <Arduino.h>


#define BUTTON_1_PIN PB13
#define BUTTON_2_PIN PB14
#define BUTTON_3_PIN PB15
#define BUTTON_4_PIN PA8


#endif

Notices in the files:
README.md:
License: GPL v3
